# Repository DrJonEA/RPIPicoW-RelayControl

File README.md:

# DrJonEA: RPIPicoW-RelayControl

A Raspberry Pi Pico W based Relay control board. Using a ULN2003 as driver for a 5Volt Relay.

Example controlling the Relay via an onboard SPST switch. Plus remote control of MQTT/TLS.

This project is featured on my [Youtube Channel DrJonEA](https://youtube.com/@drjonea).

## Clone and Build
The example is built  using the Pico SDK version 2.2.0 and a number of libraries which are included as submodules.
Please clone the repository using the recurse submodules switch. 

I've written a [blog post](https://drjonea.co.uk/2025/12/15/building-my-projects-from-repo/) on how to clone, build and 
debug my projects. It covers command line and VSCode build. I hope this help you get started.

## Schematic, PCB Design and Components
The *PCB* folder contains the KiCAD project files for the PCB Design. 

Components:

 |  Designator | Footprint | Quantity | Designation | 
 | ------------- | ----------- | ----------- | ------------ | 
 | "Id" | "Designator" | "Footprint" | "Quantity" | "Designation" | "Supplier and ref" | 
 | 1 | "C1" | "CP_Radial_D10.0mm_P5.00mm" | 1 | "1000uF" | 
 | 2 | "I2C2,I2C1" | "PinHeader_1x04_P2.54mm_Vertical" | 2 | "Conn_01x04_Pin" | 
 | 3 | "J4,J3" | "PinHeader_1x04_P2.54mm_Vertical" | 2 | "Touch Display" | 
 | 4 | "O1" | "ScrewTerm_Oiyagai_01x02_5mm" | 1 | "Elect" | 
 | 5 | "A1" | "RaspberryPi_Pico_Common_Unspecified" | 1 | "RaspberryPi_Pico" | 
 | 6 | "C2" | "C_Disc_D4.7mm_W2.5mm_P5.00mm" | 1 | "10uF" | 
 | 7 | "K1" | "Relay_SPDT_SANYOU_SRD_Series_Form_C" | 1 | "SANYOU_SRD_Form_C" |  |  | 
 | 8 | "ST1" | "ScrewTerm_Oiyagai_01x03_5mm" | 1 | "Screw_Terminal_01x03" | 
 | 9 | "U1" | "CERDIP-16_W7.62mm_SideBrazed_LongPads_Socket" | 1 | "ULN2003" | 
 | 10 | "D1" | "D_DO-41_SOD81_P10.16mm_Horizontal" | 1 | "1N4007" | 
 | 11 | "SW2" | "SW_PUSH_6mm" | 1 | "SW_SPST" | 
 | 12 | "SW1" | "SW_Latch_7x7_DPDT" | 1 | "SW_DPDT_x2" | 
 | 13 | "R4" | "R_Axial_DIN0309_L9.0mm_D3.2mm_P15.24mm_Horizontal" | 1 | "220R" | 
 | 14 | "U2" | "WS2812B Strip" | 1 | 4 LED strip at 144per meter fits | 

## Examples Projects

### exp/TestLeds
A test project to check the WS2812B LEDs and Switch on the board

### exp/TestRelay
A test projec to check the Relay works. Uses the switch to toggle the relay state. Shows the state of the
relay on the WS2812B LED

### Main Project
This is a MQTT device connecting to a MQTT Broker (I use Flespi.io). It connects over TLS using WolfSSL 
to provide a TLS connection.  The device will then take commands on the topic 
"TNG/*{DEVICEID}*/TPC/Relay/req". With a Payload as JSON saying {"on": True} or {"on": False}.

To build this examples the following environment variables are used to source credentials:

+ WIFI_SSID
+ WIFI_PASSWORD
+ MQTT_CLIENT
+ MQTT_USER
+ MQTT_PASSWD
+ MQTT_HOST
+ MQTT_PORT

I have a course showing how I build these types of MQTT Devices over on [Udemy](https://www.udemy.com/course/iot-with-rpi-pico-w/?referralCode=331C13FDD6ABC00BFB81).

### Python Control Example
Python scripts which can interact with the device are included in the *py* folder. They require the client id of
the device the are controlling in this form:

python3 on.py *{DEVICE_ID}*

The scripts take credentials for the client from the followin environment variables:

+ MQTT_USER
+ MQTT_PASSWD
+ MQTT_HOST
+ MQTT_PORT

NOTE: To use MQTT the device and the client must have different Client IDs (or MQTT_USER).

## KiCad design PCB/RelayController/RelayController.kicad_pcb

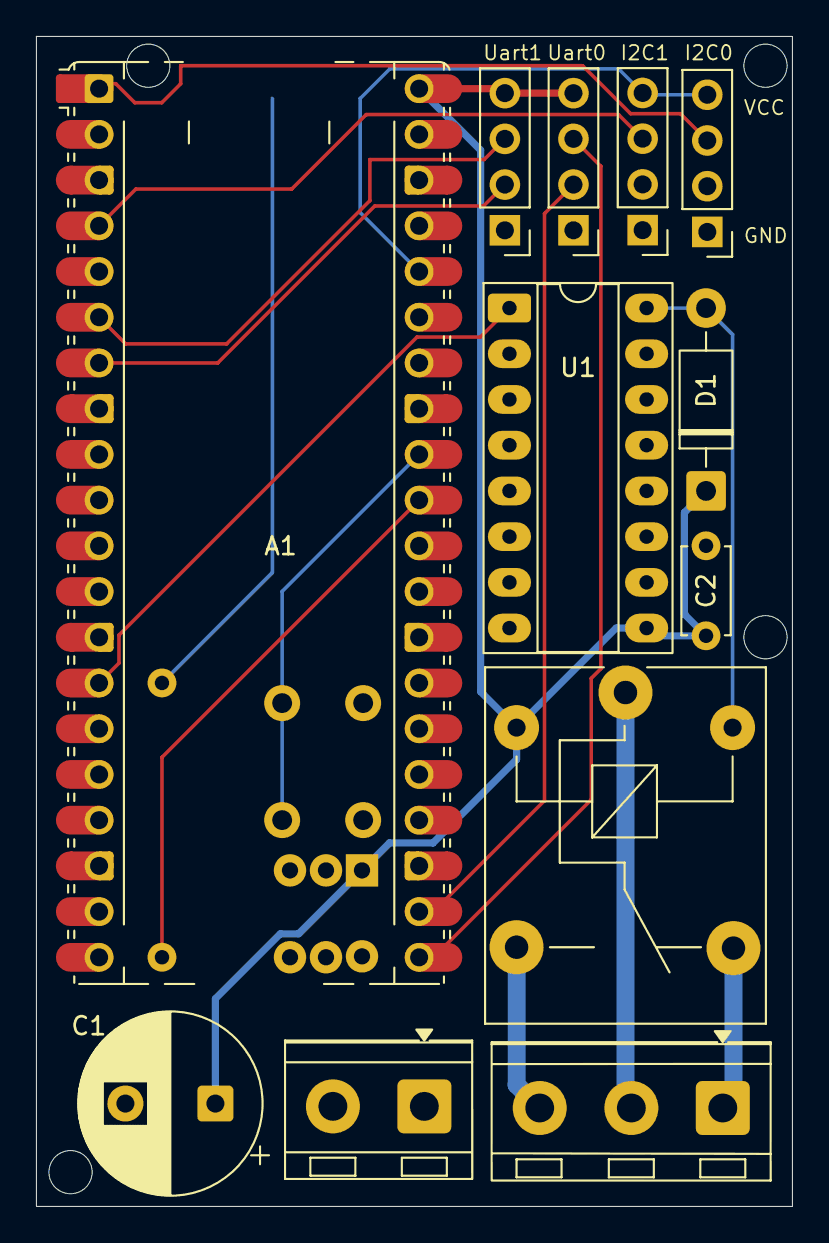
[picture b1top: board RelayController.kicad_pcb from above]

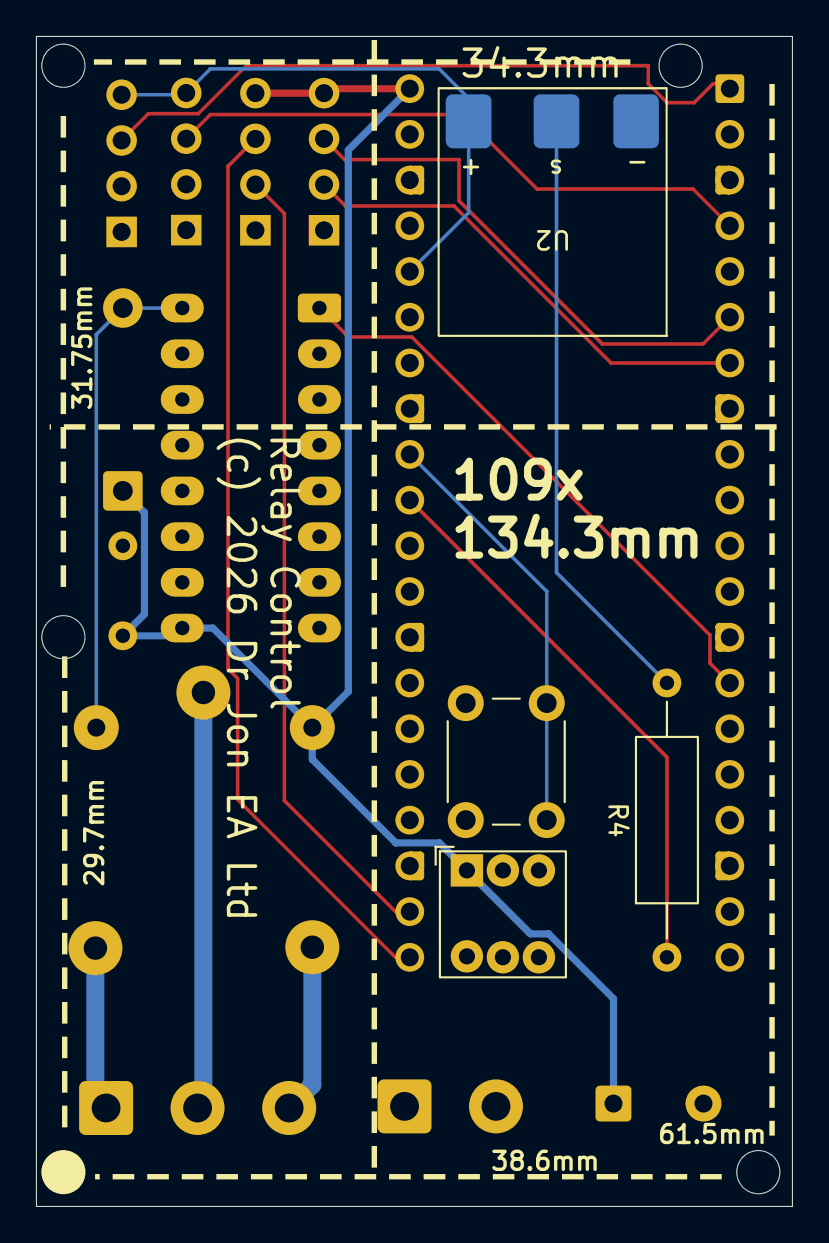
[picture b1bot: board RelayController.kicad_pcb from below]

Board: 4 copper layers, 42.0 x 65.0 mm, 16 parts (4 on the bottom side), 20 nets.

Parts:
A1: RaspberryPi_Pico; RaspberryPi_Pico_Common_Unspecified
C1: 1000uF; CP_Radial_D10.0mm_P5.00mm
C2: 10uF; C_Disc_D4.7mm_W2.5mm_P5.00mm
D1: 1N4007; D_DO-41_SOD81_P10.16mm_Horizontal
I2C1, I2C2: Conn_01x04_Pin; PinHeader_1x04_P2.54mm_Vertical
J3, J4: Touch Display; PinHeader_1x04_P2.54mm_Vertical
K1: SANYOU_SRD_Form_C; Relay_SPDT_SANYOU_SRD_Series_Form_C
O1: Elect; ScrewTerm_Oiyagai_01x02_5mm
R4: 220R; R_Axial_DIN0309_L9.0mm_D3.2mm_P15.24mm_Horizontal
ST1: Screw_Terminal_01x03; ScrewTerm_Oiyagai_01x03_5mm
SW1: SW_DPDT_x2; SW_Latch_7x7_DPDT
SW2: SW_SPST; SW_PUSH_6mm
U1: ULN2003; CERDIP-16_W7.62mm_SideBrazed_LongPads_Socket
U2: WS2812B Strip

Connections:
+3V3: A1.36 (3V3), I2C1.4 (VCC), I2C2.4 (VCC), U2.3 (VCC)
+5V: A1.40 (VBUS), C1.1, C2.1, D1.1 (K), J3.4, J4.4, K1.2, SW1.1 (A), U1.9 (COM)
/K1: A1.14 (GPIO10), U1.1 (I1)
/K1Coil: D1.2 (A), K1.5, U1.16 (O1)
/RX0: A1.22 (GPIO17), J4.2
/RX1: A1.7 (GPIO5), J3.2
/SW2: A1.32 (GPIO27_ADC1), SW2.2 (B)
/TX0: A1.21 (GPIO16), J4.3
/TX1: A1.6 (GPIO4), J3.3
/scl0: A1.2 (GPIO1), I2C1.2 (SCL)
/scl1: A1.5 (GPIO3), I2C2.2 (SCL)
/sda0: A1.1 (GPIO0), I2C1.3 (SDA)
/sda1: A1.4 (GPIO2), I2C2.3 (SDA)
GND: A1.3 (GND), A1.8 (GND), A1.13 (GND), A1.18 (GND), A1.23 (GND), A1.28 (GND), A1.38 (GND), C1.2, C2.2, I2C1.1 (GND), I2C2.1 (GND), J3.1, J4.1, O1.1, SW2.1 (A), U1.8 (GND), U2.1 (GND)
unnamed: A1.31 (GPIO26_ADC0), R4.1
unnamed: O1.2, SW1.2 (B)
unnamed: K1.4, ST1.1
unnamed: K1.1, ST1.2
unnamed: K1.3, ST1.3
unnamed: R4.2, U2.2 (In)

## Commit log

2026-03-22 Board Tests
2026-03-23 Working demo version

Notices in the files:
PCB/RelayController/RelayController.kicad_pcb:
(c) 2026 Dr Jon EA Ltd
